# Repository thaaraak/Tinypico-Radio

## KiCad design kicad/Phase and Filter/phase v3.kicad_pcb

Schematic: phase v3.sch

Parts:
C1, C5: .010uF; Capacitor 0805
C2, C3, C6, C8, C10, C16: .1uF; Capacitor 0805
C4: 10nF; Capacitor 0805
C7, C11, C12: 1nF; Capacitor 0805
C9, C13: 10uF; CPOL-RADIAL-2.5MM-5MM
C14, C15: 1.5nF; Capacitor 0805
J1, J2: AUDIO_JACK_3.5MM_KIT; AUDIO-JACK-KIT
J3, J4: Pad
R1: 9.53k; Resistor 0805
R2, R3, R5, R9, R11, R12, R17, R18, R19: 10k; Resistor 0805
R4: 115k; Resistor 0805
R6: 3.3k; Resistor 0805
R7: 2.32k; Resistor 0805
R8: 28k; Resistor 0805
R10, R13, R14: 1k; Resistor 0805
R15: 120k; Resistor 0805
R16: 33k; Resistor 0805
R20, R22: 68k; Resistor 0805
R21: 100k; Resistor 0805
R23: 150k; Resistor 0805
R24: 220k; Resistor 0805
U1, U4: LM358DIP08-SOIC; SO08
U2, U3: LM358; SO08
VR1: 50k; TRIMPOT-PTH-3386U
VR2: 500k; TRIMPOT-PTH-3386U
VR3: 500; TRIMPOT-PTH-3386U

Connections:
+6V: C13.2, R17.1, R19.2, R20.2, R23.2, U2.5 (+IN), U3.3 (+IN), U3.5 (+IN)
+12V: C3.1, C6.1, C8.1, C9.2, J3.1, R17.2, U1.8 (P$V+), U2.8 (P$V+), U3.8 (P$V+), U4.8 (P$V+)
GND: C1.2, C2.2, C3.2, C4.2, C5.2, C6.2, C8.2, C9.1, C13.1, J1.SLEEVE, J2.SLEEVE, J4.1, R19.1, U1.4 (P$V-), U2.4 (P$V-), U3.4 (P$V-), U4.4 (P$V-)
unnamed: C1.1, R8.2, U1.5 (+IN)
unnamed: C2.1, R4.2, U4.5 (+IN), VR2.3
unnamed: C4.1, R1.2, U4.3 (+IN), VR1.3
unnamed: C5.1, R7.2, U1.3 (+IN)
unnamed: C7.1, R14.2, R15.1, U2.6 (-IN)
unnamed: C7.2, R15.2, U2.3 (+IN), U2.7 (OUT)
unnamed: C10.1, C14.2, R24.1, U3.7 (OUT)
unnamed: C10.2, R14.1
unnamed: C11.1, C12.1, R16.2, R20.1
unnamed: C11.2, R21.1, R22.1, U3.1 (OUT)
unnamed: C12.2, R21.2, U3.2 (-IN)
unnamed: C14.1, C15.1, R22.2, R23.1
unnamed: C15.2, R24.2, U3.6 (-IN)
unnamed: C16.1, VR3.2
unnamed: C16.2, R16.1
unnamed: J1.RING, R1.1, R2.1, VR1.1, VR1.2
unnamed: J1.TIP, R7.1, R18.1
unnamed: J2.RING, J2.RSH, J2.TIP, J2.TSH, U2.1 (OUT), U2.2 (-IN)
unnamed: R2.2, R3.1, U4.2 (-IN)
unnamed: R3.2, R4.1, R5.1, U4.1 (OUT), VR2.1, VR2.2
unnamed: R5.2, R6.1, U4.6 (-IN)
unnamed: R10.1, VR3.3
unnamed: R10.2, R12.2, U1.7 (OUT)
unnamed: R8.1, R9.2, R11.1, U1.1 (OUT)
unnamed: R11.2, R12.1, U1.6 (-IN)
unnamed: R6.2, R13.1, U4.7 (OUT)
unnamed: R13.2, VR3.1
unnamed: R9.1, R18.2, U1.2 (-IN)

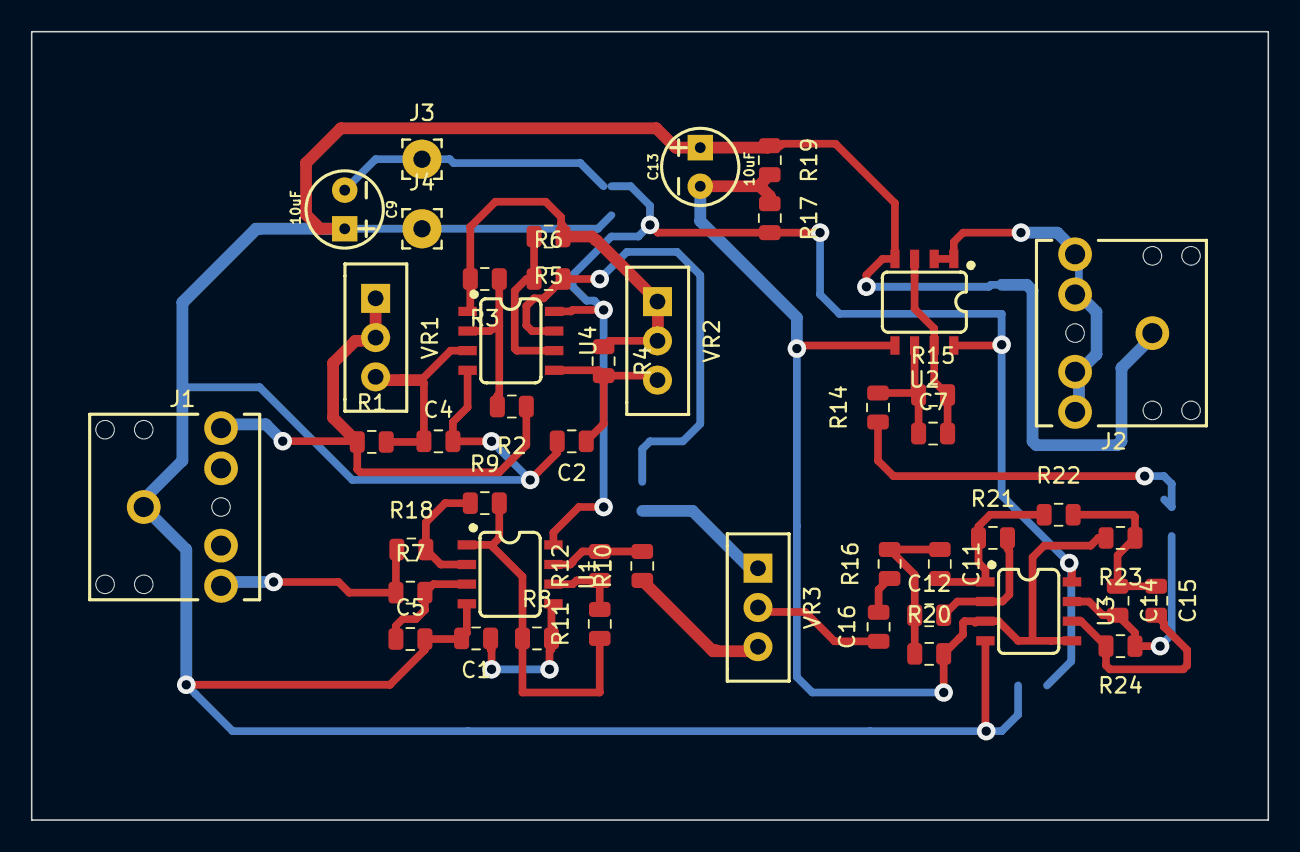
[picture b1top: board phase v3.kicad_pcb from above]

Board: 2 copper layers, 80.0 x 51.0 mm, 51 parts (0 on the bottom side), 31 nets.

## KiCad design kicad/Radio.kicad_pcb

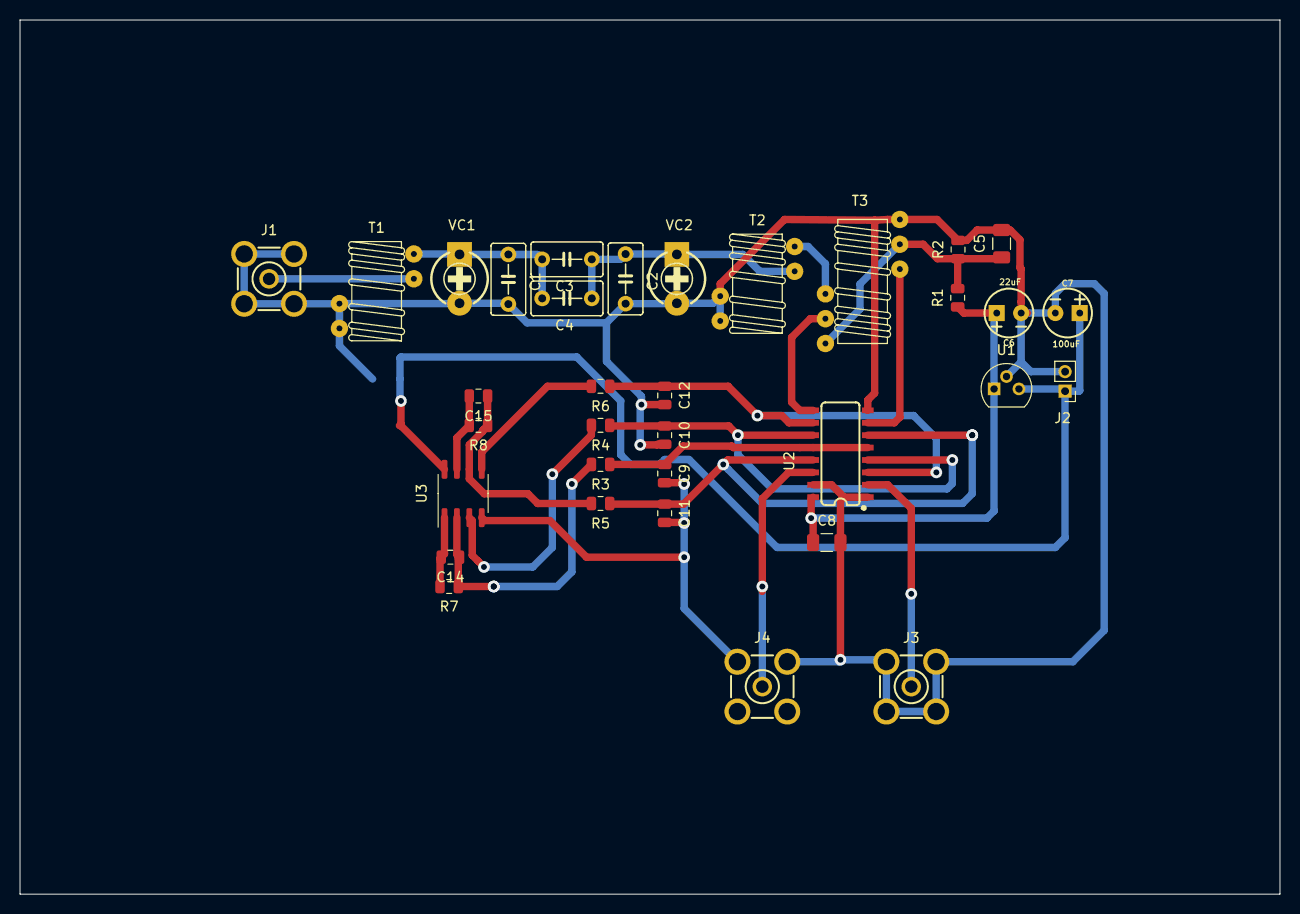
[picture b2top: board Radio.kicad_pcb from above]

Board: 2 copper layers, 129.0 x 89.5 mm, 35 parts (1 on the bottom side), 22 nets.

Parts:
C1, C2: 150pF; Capacitor
C3: 5pF; Capacitor
C4: 10pF; Capacitor
C5, C8, C13: .1uF; Capacitor 1206
C6: 22uF; CPOL-RADIAL-2.5MM-5MM
C7: 100uF; CPOL-RADIAL-2.5MM-5MM
C9, C10, C11, C12: 470nF; Capacitor 0805
C14, C15: 1nF; Capacitor 0805
J1, J3, J4: PCB_SMA; PCB SMA
J2: Conn_01x02; Power Connector
R1, R2, R7, R8: 10k; Capacitor 0805
R3, R4, R5, R6: 100; Capacitor 0805
T1: 6:31; T37 Transformer
T2: 31:6; T37 Transformer
T3: T50_SPLITTER; T50 Trifilar
U1: LM78L05_TO92; T092
U2: FST3253; SO16
U3: LM358; SOIC8
VC1, VC2: 40pF; trimcap

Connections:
+5V: C6.1, C8.1, R1.1, U1.1, U2.16
+12V: C7.1, C13.1, J2.1, U1.3, U3.8
GND: C1.2, C2.2, C5.2, C6.2, C7.2, C8.2, C9.2, C10.2, C11.2, C12.2, C13.2, J1.2, J1.3, J1.4, J1.5, J2.2, J3.2, J3.3, J3.4, J3.5, J4.2, J4.3, J4.4, J4.5, R2.2, T1.C1A, T1.C2A, T2.C1A, T2.C2A, T3.C1A, U1.2, U2.1, U2.8, U2.15, U3.4, VC1.2, VC2.2
unnamed: C1.1, C3.2, C4.2, T1.C2B, VC1.1
unnamed: C2.1, C3.1, C4.1, T2.C1B, VC2.1
unnamed: C5.1, R1.2, R2.1, T3.C2A, T3.C3B
unnamed: C9.1, R3.1, U2.5, U2.12
unnamed: C10.1, R4.1, U2.4, U2.11
unnamed: C11.1, R5.1, U2.6, U2.13
unnamed: C12.1, R6.1, U2.3, U2.10
unnamed: C14.1, R3.2, R7.1, U3.2
unnamed: C14.2, R7.2, U3.1
unnamed: C15.1, R5.2, R8.1, U3.6
unnamed: C15.2, R8.2, U3.7
unnamed: J1.1, T1.C1B
unnamed: J3.1, U2.2
unnamed: J4.1, U2.14
unnamed: R4.2, U3.3
unnamed: R6.2, U3.5
unnamed: T2.C2B, T3.C1B
unnamed: T3.C2B, U2.9
unnamed: T3.C3A, U2.7
